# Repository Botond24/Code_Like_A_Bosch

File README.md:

# Code Like A Bosch Challenge
## Hardware Chalenge
### Ideas
- lapma
- toldo
- nyomatek kijelzo
- Nekem az ötletem a szogmérő, ezt 2 dologra is használhatjuk
    - Egyrészt segíthet kezdőknek hogy jól tartsák a fúrót
    - Másrészt vízszint mérő

### TODO -- Moved to Obsidian/Main doc.md

1. Brainstorm and decide on an idea that can enhance the Bosch 12 screwdriver
    - Business model of your solution
    - Customer need for your extension – how many new customers could be acquired with the new extension
    - Value added for the customer – comfort, safety, efficiency, versatility
    - Feasibility – is this can be really realized?
    - Costs – development, BOM, sale price
2. Overview of the proposed solution – block diagram, infographics, etc.
3. Schematic of the proposed solution – the real connection between the components, modules, can be done in CAD, or in paint.
4. Simulations and calculations of the main component, or part of the hardware (if applicable)
5. Documentation of your idea and solution
6. Firmware block diagram (only if applicable to your idea)
7. Firmware code, or segment of your algorithm (only if applicable to your idea)
8. Explain your idea and introduce your team in a video
9. Optional for additional points: start prototyping and bring your idea to life with the provided tools, hardware components on site (HW + firmware)

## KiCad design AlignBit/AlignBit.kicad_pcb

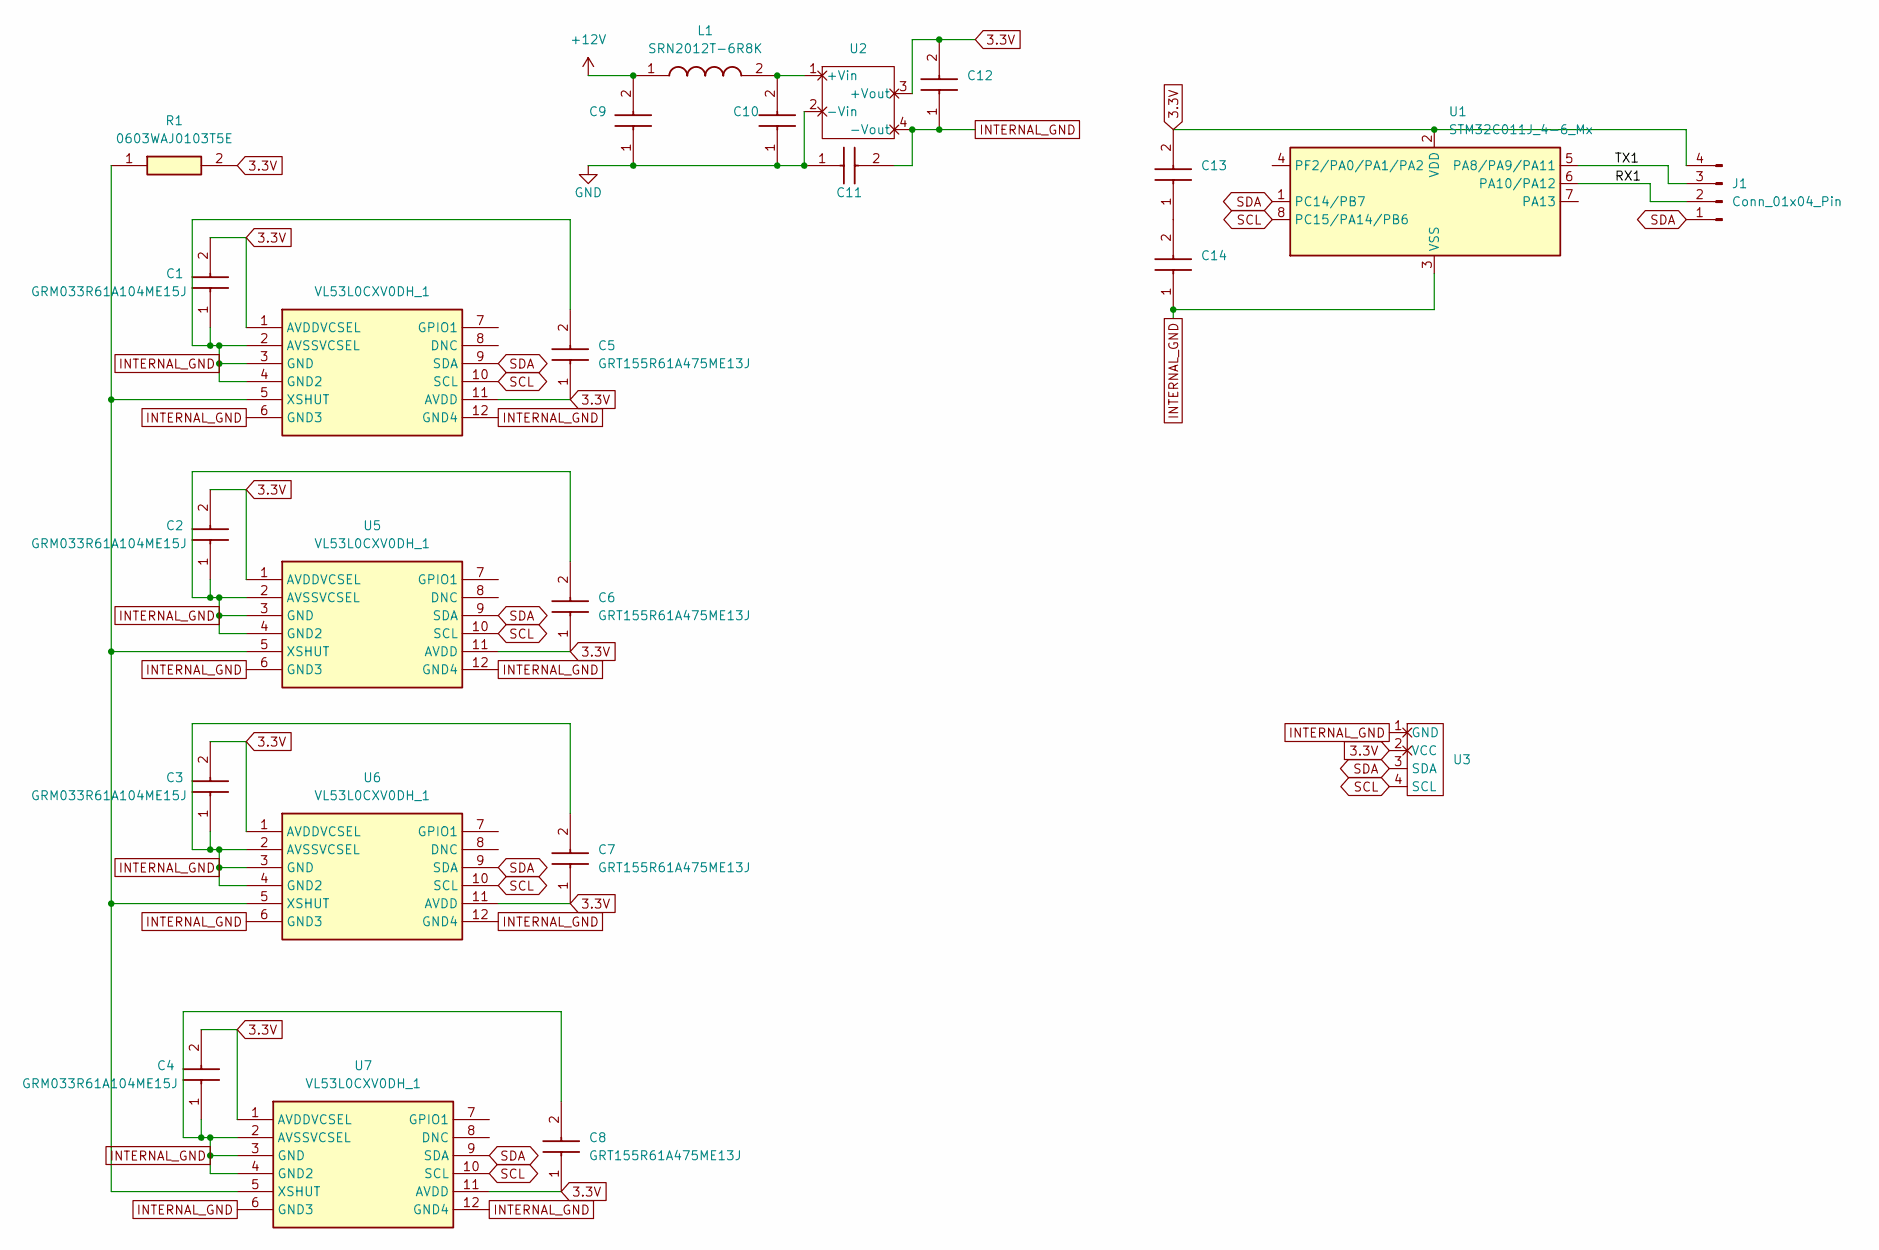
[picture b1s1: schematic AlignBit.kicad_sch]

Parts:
C1, C2, C3, C4, C9, C10, C13: GRM033R61A104ME15J; CAPC0603X33N; Mouser Part Number 81-GRM033R61A104ME5J
C5, C6, C7, C8, C14: GRT155R61A475ME13J; CAPC1005X55N; Mouser Part Number 81-GRT155R61A475ME3J
C11: C0402C271K5RAC; CAPC1005X55N; Mouser Part Number 80-C0402C271K5RAC
C12: GRM188R61C106MA73J; CAPC1608X90N; Mouser Part Number 81-GRM188R61C106MA3J
J1: Conn_01x04_Pin; PinSocket_1x04_P1.00mm_Vertical
L1: SRN2012T-6R8K; INDPM2012X120N; Mouser Part Number 652-SRN2012T-6R8K
R1: 0603WAJ0103T5E; RESC1608X55N; Mouser Part Number 303-0603WAJ0103T5E
U1: STM32C011J_4-6_Mx; SOIC-8_3.9x4.9mm_P1.27mm
U2: IEB01
U3: PinSocket_1x04_P1.00mm_Vertical
U4, U5, U6, U7: VL53L0CXV0DH_1; LGA12_1; Mouser Part Number 511-VL53L0CXV0DH/1

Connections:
3.3V: C1.2, C2.2, C3.2, C4.2, C5.1, C6.1, C7.1, C8.1, C12.2, C13.2, J1.4, R1.2, U1.2 (VDD), U2.3 (+Vout), U3.2 (VCC), U4.1 (AVDDVCSEL), U4.11 (AVDD), U5.1 (AVDDVCSEL), U5.11 (AVDD), U6.1 (AVDDVCSEL), U6.11 (AVDD), U7.1 (AVDDVCSEL), U7.11 (AVDD)
+12V: C9.2, L1.1
/RX1: J1.2, U1.6 (PA10/PA12)
/TX1: J1.3, U1.5 (PA8/PA9/PA11)
GND: C9.1, C10.1, C11.1, U2.2 (-Vin); also elsewhere on the board
INTERNAL_GND: C1.1, C2.1, C3.1, C4.1, C5.2, C6.2, C7.2, C8.2, C11.2, C12.1, C14.1, U1.3 (VSS), U2.4 (-Vout), U3.1 (GND), U4.2 (AVSSVCSEL), U4.3 (GND), U4.4 (GND2), U4.6 (GND3), U4.12 (GND4), U5.2 (AVSSVCSEL), U5.3 (GND), U5.4 (GND2), U5.6 (GND3), U5.12 (GND4), U6.2 (AVSSVCSEL), U6.3 (GND), U6.4 (GND2), U6.6 (GND3), U6.12 (GND4), U7.2 (AVSSVCSEL), U7.3 (GND), U7.4 (GND2), U7.6 (GND3), U7.12 (GND4)
unnamed: C13.1, C14.2
unnamed 7: C10.2, L1.2, U2.1 (+Vin); also elsewhere on the board
unnamed: R1.1, U4.5 (XSHUT), U5.5 (XSHUT), U6.5 (XSHUT), U7.5 (XSHUT)
SCL: U1.8 (PC15/PA14/PB6), U3.4 (SCL), U4.10 (SCL), U5.10 (SCL), U6.10 (SCL), U7.10 (SCL)
SDA: J1.1, U1.1 (PC14/PB7), U3.3 (SDA), U4.9 (SDA), U5.9 (SDA), U6.9 (SDA), U7.9 (SDA)

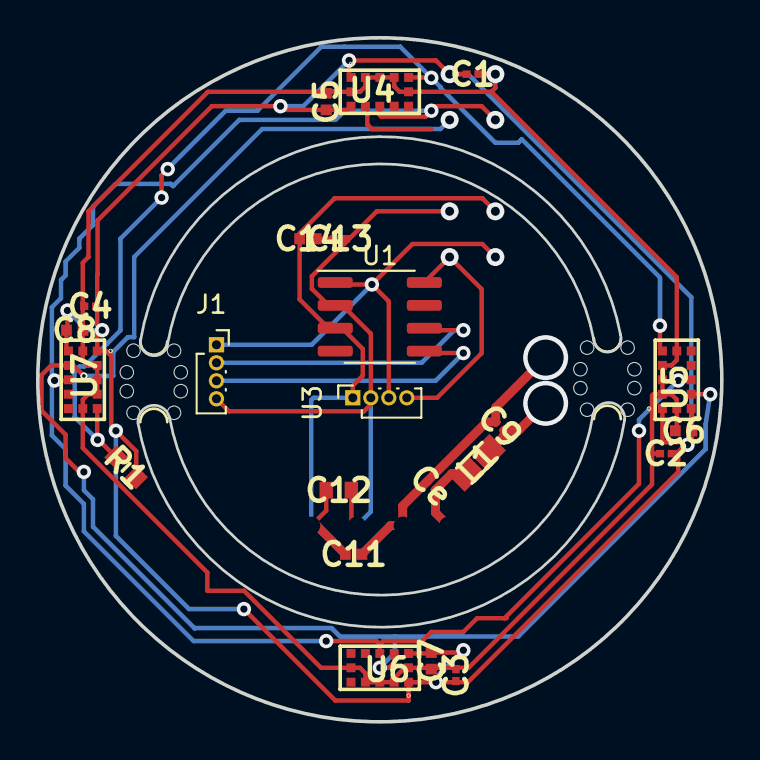
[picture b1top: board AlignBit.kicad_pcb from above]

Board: 2 copper layers, 38.0 x 38.0 mm, 26 parts (1 on the bottom side), 11 nets.

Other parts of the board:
Ce: GRM033R61A104ME15J; CAPC0603X33N
mouse-bite-1.5mm-slot, mouse-bite-1.5mm-slot#2: VAL**; mouse-bite-1.5mm-slot

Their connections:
GND: Ce.1; also elsewhere on the board
unnamed 7: Ce.2; also elsewhere on the board

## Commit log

2023-09-29 todo
2023-09-29 Update todo
2023-09-29 igen
2023-09-29 added ideas
2023-09-29 fixed ordering
2023-09-29 added real todo
2023-09-29 Obsidian
2023-09-29 added rest of needs
2023-09-29 adding values
2023-09-29 adding md
2023-09-29 adding overview
2023-09-29 fix typo
2023-09-29 Strated Schematic
2023-09-30 adding kernel
2023-09-30 swiching
2023-09-30 change address
2023-09-30 uploading displays
2023-09-30 Lots finished
    Final name
    Schematic
    PCB
    Business model
    Cost
2023-09-30 clean up
2023-09-30 Finsihed 2 more requirements
2023-09-30 firmware diagram
2023-09-30 Adding things untill its done
2023-09-30 uploading
2023-09-30 Bom is the only left
2023-09-30 Finished Documentation
2023-09-30 adding ppt
2023-10-03 Create shork
